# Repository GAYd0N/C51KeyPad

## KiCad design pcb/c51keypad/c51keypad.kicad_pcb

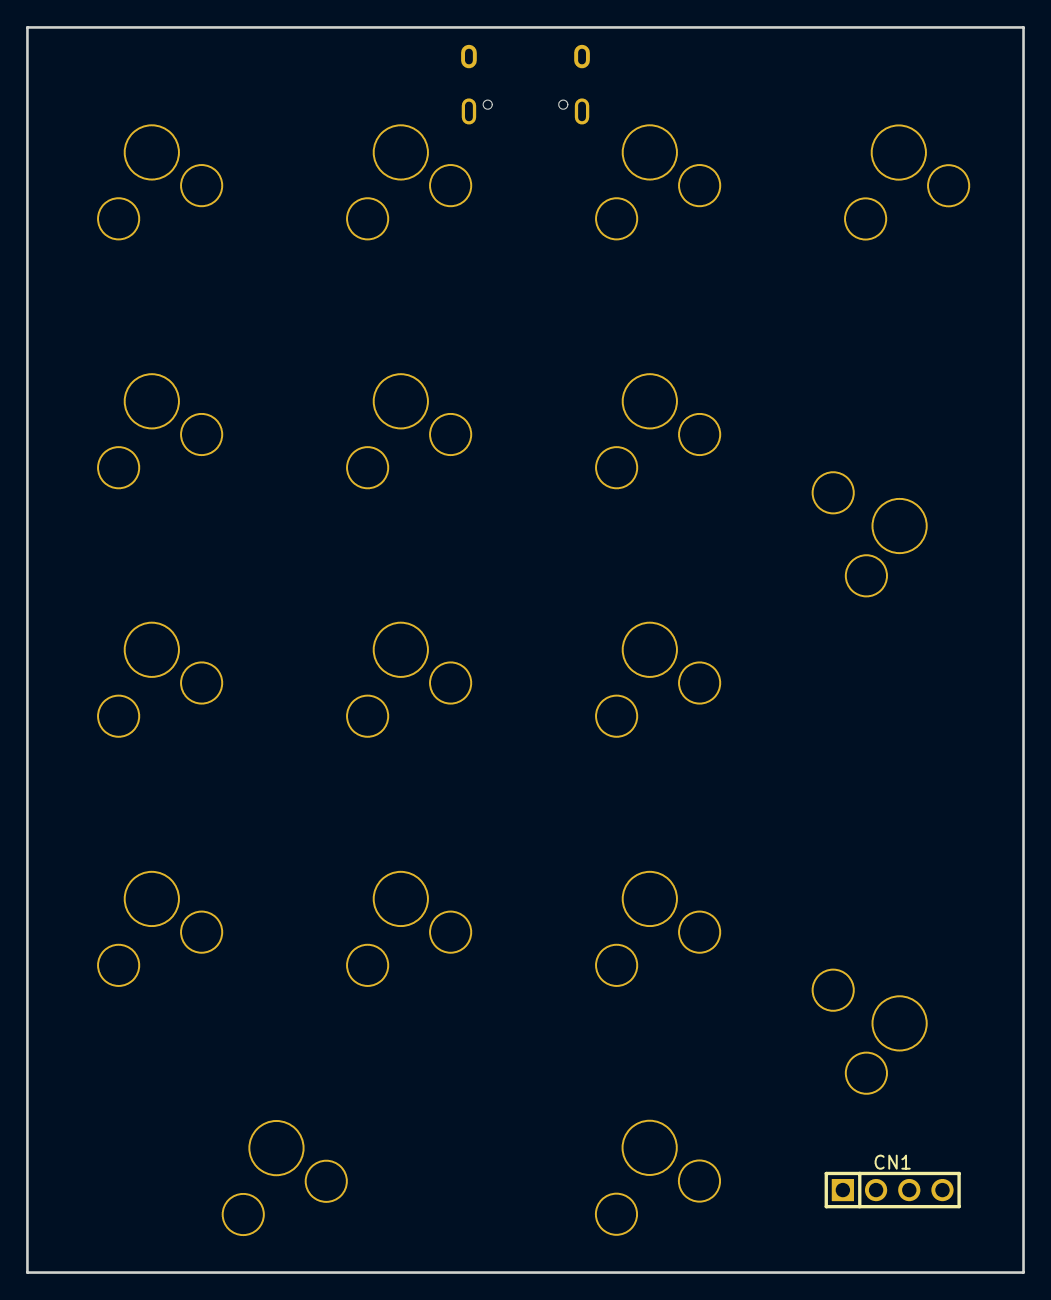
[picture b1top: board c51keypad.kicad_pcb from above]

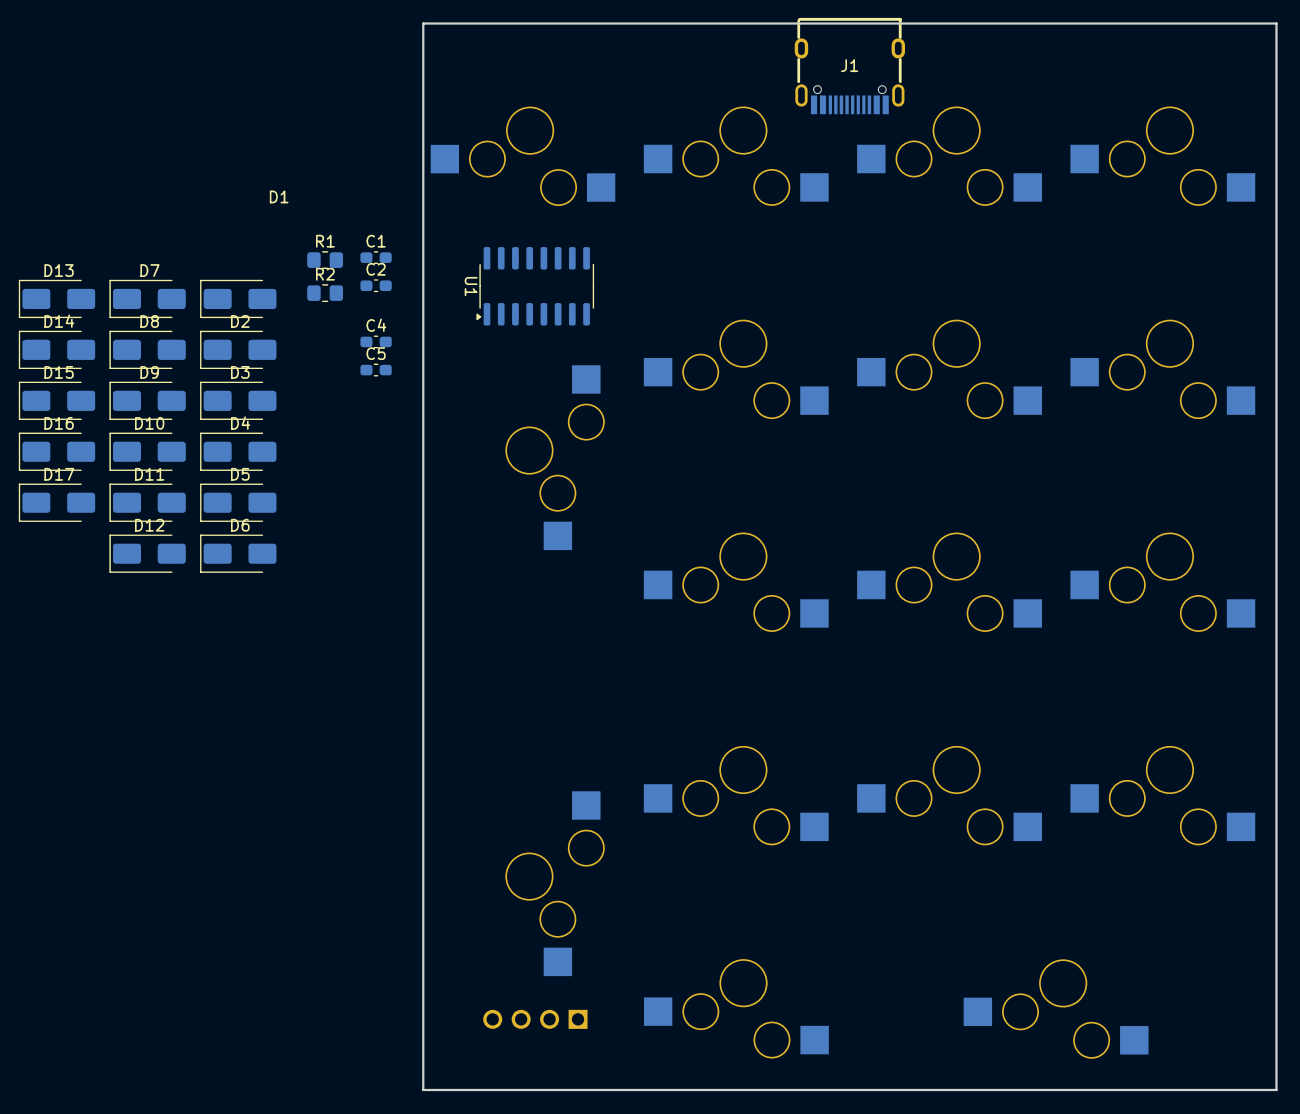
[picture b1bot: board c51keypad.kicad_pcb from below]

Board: 2 copper layers, 76.2 x 95.2 mm, 43 parts (25 on the bottom side), 35 nets, no tracks yet.

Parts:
C1, C4: 0.1uF; C_0603_1608Metric_Pad1.08x0.95mm_HandSolder
C2: 200pF; C_0603_1608Metric_Pad1.08x0.95mm_HandSolder
C5: 10uF; C_0603_1608Metric_Pad1.08x0.95mm_HandSolder
CN1: PZ254V-11-04P; HDR-TH_4P-P2.54-V-M
D1, D2, D3, D4, D5, D6, D7, D8, D9, D10, D11, D12, D13, D14, D15, D16, D17: D; D_SMA
J1: USB_C_Receptacle_USB2.0_16P; USB-C-SMD_TYPE-C-6PIN-2MD-073
R1, R2: 5.1k; R_0805_2012Metric_Pad1.20x1.40mm_HandSolder
SW1, SW2, SW3, SW4, SW5, SW6, SW7, SW8, SW9, SW10, SW11, SW12, SW13, SW14, SW15, SW16, SW17: 凯华轴座
U1: CH9328; SOP-16_3.9x9.9mm_P1.27mm

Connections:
/COL0: SW1.1, SW5.1, SW9.1, SW13.1, SW17.1
/COL1: SW2.1, SW6.1, SW10.1, SW14.1
/COL2: SW3.1, SW7.1, SW11.1, SW15.1
/COL3: SW4.1, SW8.1, SW12.1, SW16.1
/D+: J1.6 (DP1), J1.8 (DP2), U1.6 (UD+)
/D-: J1.5 (DN2), J1.7 (DN1), U1.7 (UD-)
/ROW0: D1.1 (K), D2.1 (K), D3.1 (K), D4.1 (K)
/ROW1: D5.1 (K), D6.1 (K), D7.1 (K), D8.1 (K)
/ROW2: D9.1 (K), D10.1 (K), D11.1 (K), D12.1 (K)
/ROW3: D13.1 (K), D14.1 (K), D15.1 (K), D16.1 (K)
/RXD: CN1.1, U1.2 (TXD)
/TXD: CN1.2, U1.3 (RXD)
/VBUS: C4.2, C5.2, CN1.3, J1.2 (VBUS), J1.11 (VBUS), U1.11 (IO2), U1.12 (IO1), U1.13 (IO4), U1.15 (VCC)
GND: C1.1, C2.2, C4.1, C5.1, CN1.4, J1.1 (GND), J1.12 (GND), J1.13 (GND), J1.14 (SHIELD), R1.2, R2.2, U1.8 (GND), U1.14 (IO3)
unnamed: D1.2 (A), SW1.2
unnamed: D2.2 (A), SW2.2
unnamed: D3.2 (A), SW3.2
unnamed: D4.2 (A), SW4.2
unnamed: D5.2 (A), SW5.2
unnamed: D6.2 (A), SW6.2
unnamed: D7.2 (A), SW7.2
unnamed: D8.2 (A), SW8.2
unnamed: D9.2 (A), SW9.2
unnamed: D10.2 (A), SW10.2
unnamed: D11.2 (A), SW11.2
unnamed: D12.2 (A), SW12.2
unnamed: D13.2 (A), SW13.2
unnamed: D14.2 (A), SW14.2
unnamed: D15.2 (A), SW15.2
unnamed: D16.2 (A), SW16.2
unnamed: D17.2 (A), SW17.2
unnamed: J1.4 (CC1), R1.1
unnamed: J1.10 (CC2), R2.1
unnamed: C2.1, U1.1 (RSTI)
unnamed: C1.2, U1.5 (V3)

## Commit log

2024-09-30 stc15
2024-09-30 内存优化
